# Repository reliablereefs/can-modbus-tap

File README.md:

# CAN / MODBUS tap

Listen-only probe for a 24 V accessory port that uses a USB-A shell. An ESP32-S3 records classic CAN frames, a collector stores them, and MODBUS RTU payloads inside those frames are decoded into request/response pairs and a register map.

The probe cannot transmit. The isolated CAN transceiver's TXD pin is tied to its logic supply, so the driver stays recessive, and the ESP32 TWAI controller runs in listen-only mode. Use it on equipment you are allowed to monitor.

## Bring-up before any connection

The USB-A plug is not USB. Do not plug it into a computer, and do not use a normal USB cable between the equipment port and anything else. A 24 V pin in that shell will damage a USB host.

1. With the tap unplugged, meter the equipment port.
2. Identify ground and the pin that sits near 24 V.
3. Scope the other two pins. Classic CAN idle holds both near 2.5 V. RS-485 idle is a differential offset without that 2.5 V pair bias.
4. Wire the tap's USB-A plug to match the measured port: pin 1 = 24 V, pin 2 = CANL, pin 3 = CANH, pin 4 = GND. See [docs/hardware.md](docs/hardware.md).
5. Power the tap from its USB-C port. The 24 V pin is measured and is not the tap's supply.
6. Confirm frames in the collector before trusting a bitrate lock.

If the scope does not show CAN bias, stop. This board's controller only decodes classic CAN. An RS-485 MODBUS RTU pair needs a different transceiver.

## Layout

```text
can-modbus-tap/
  docs/hardware.md     board, pinout, isolation, BOM notes
  docs/protocol.md     capture record, upload JSON, MODBUS pairing
  hardware/bom.csv
  firmware/            ESP-IDF project for ESP32-S3
  collector/           SQLite ingest, decode, and browser UI
```

```mermaid
flowchart LR
  port["Equipment port"] --> choke["Choke and TVS"]
  choke --> iso["ISO1042 TXD tied high"]
  iso --> esp["ESP32-S3 listen-only"]
  v24["24 V divider"] --> adc["ADS1115"]
  adc --> i2c["ISO1640"]
  i2c --> esp
  esp --> flash["Flash ring"]
  esp --> col["Collector"]
```

## Firmware

Requires ESP-IDF 5.3. The Wi-Fi SSID and collector URL are compile-time settings, so they stay out of the git tree.

```bash
cd firmware
idf.py set-target esp32s3
idf.py menuconfig   # CAN MODBUS Tap
idf.py build flash monitor
```

Set the SSID, password, and `TAP_COLLECTOR_URL`. Leave bitrate at 0 to scan 25 kbit/s through 1 Mbit/s. Set a fixed rate once the bus is identified. An empty SSID still records to the on-module flash ring.

The activity LED (GPIO2) stays on while frames arrive. GPIO5 is the TWAI transmit test point and is not routed to the transceiver.

## Collector

```bash
cd collector
go run ./cmd/collector -listen 0.0.0.0:8080 -db data/tap.db
```

Open `http://127.0.0.1:8080/`. Pages:

| Path | Contents |
| --- | --- |
| `/` | Raw CAN frames |
| `/modbus` | CRC-valid MODBUS RTU payloads |
| `/transactions` | Request paired with the next response, 500 ms window |
| `/map` | Register addresses sorted by how often they appear |
| `/v1/frames.csv` | Recent raw frames |

`POST /v1/frames` has no authentication. Run the collector on the lab network. Details are in [docs/protocol.md](docs/protocol.md).

```bash
cd collector && go test ./...
```

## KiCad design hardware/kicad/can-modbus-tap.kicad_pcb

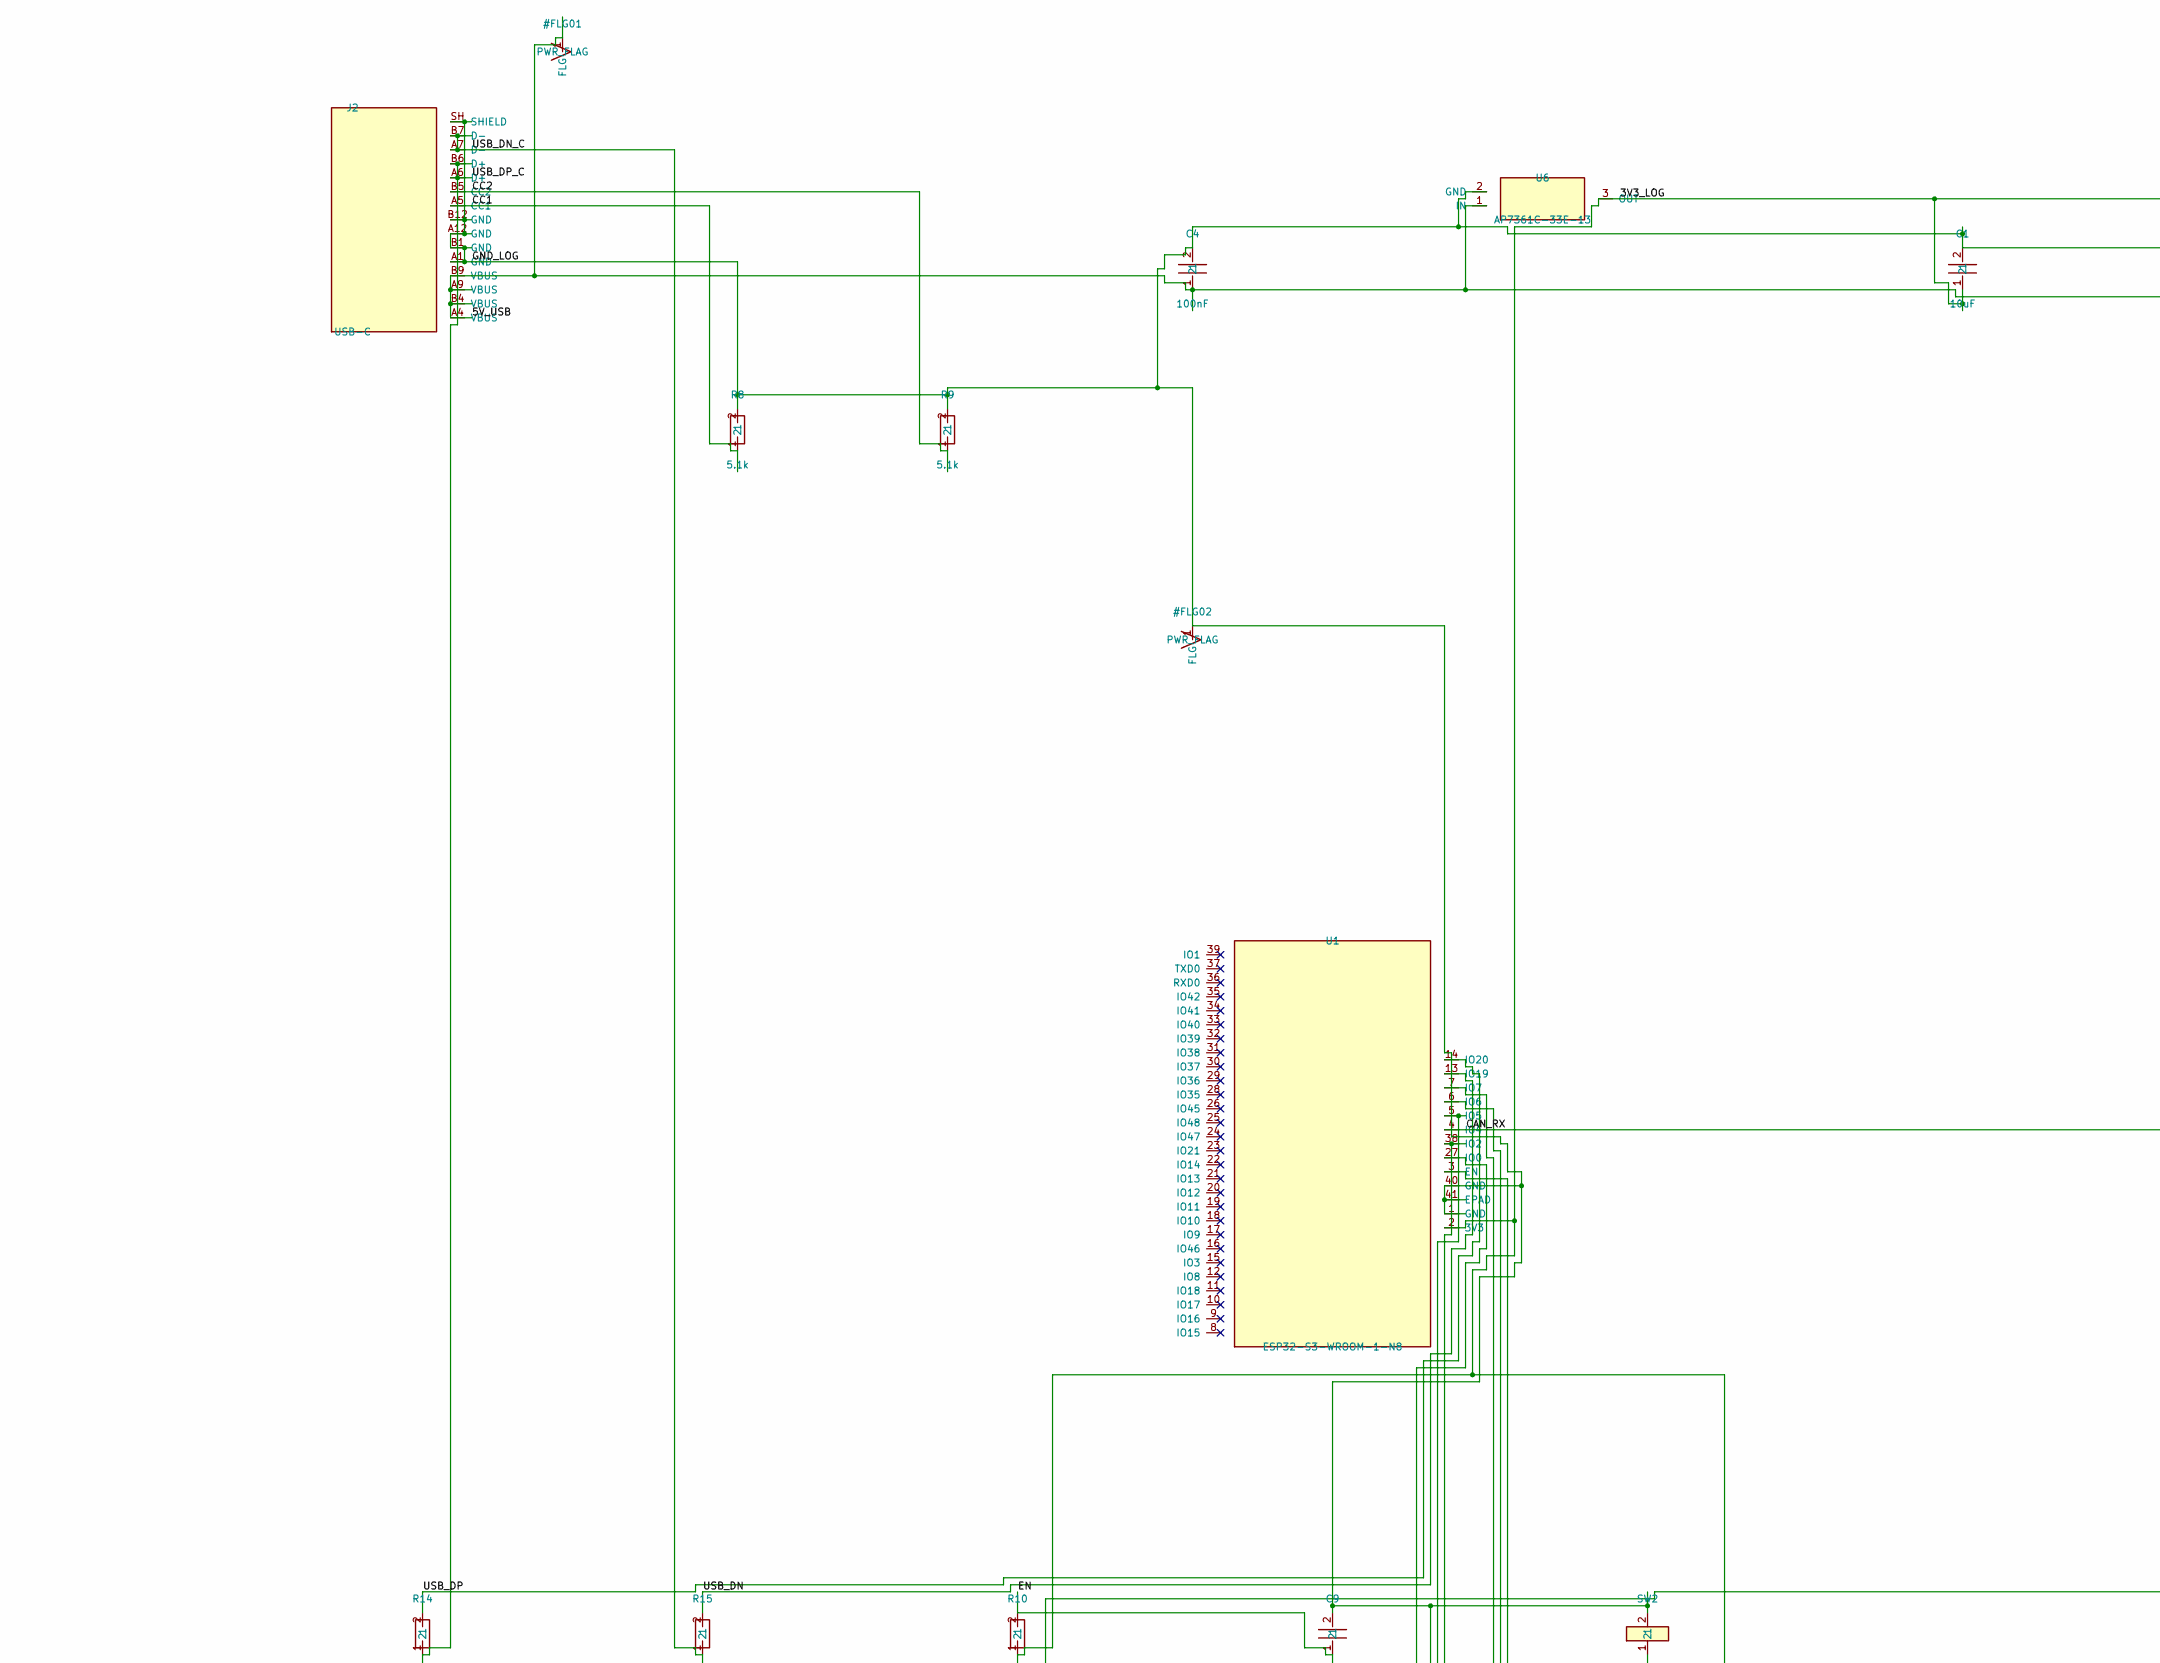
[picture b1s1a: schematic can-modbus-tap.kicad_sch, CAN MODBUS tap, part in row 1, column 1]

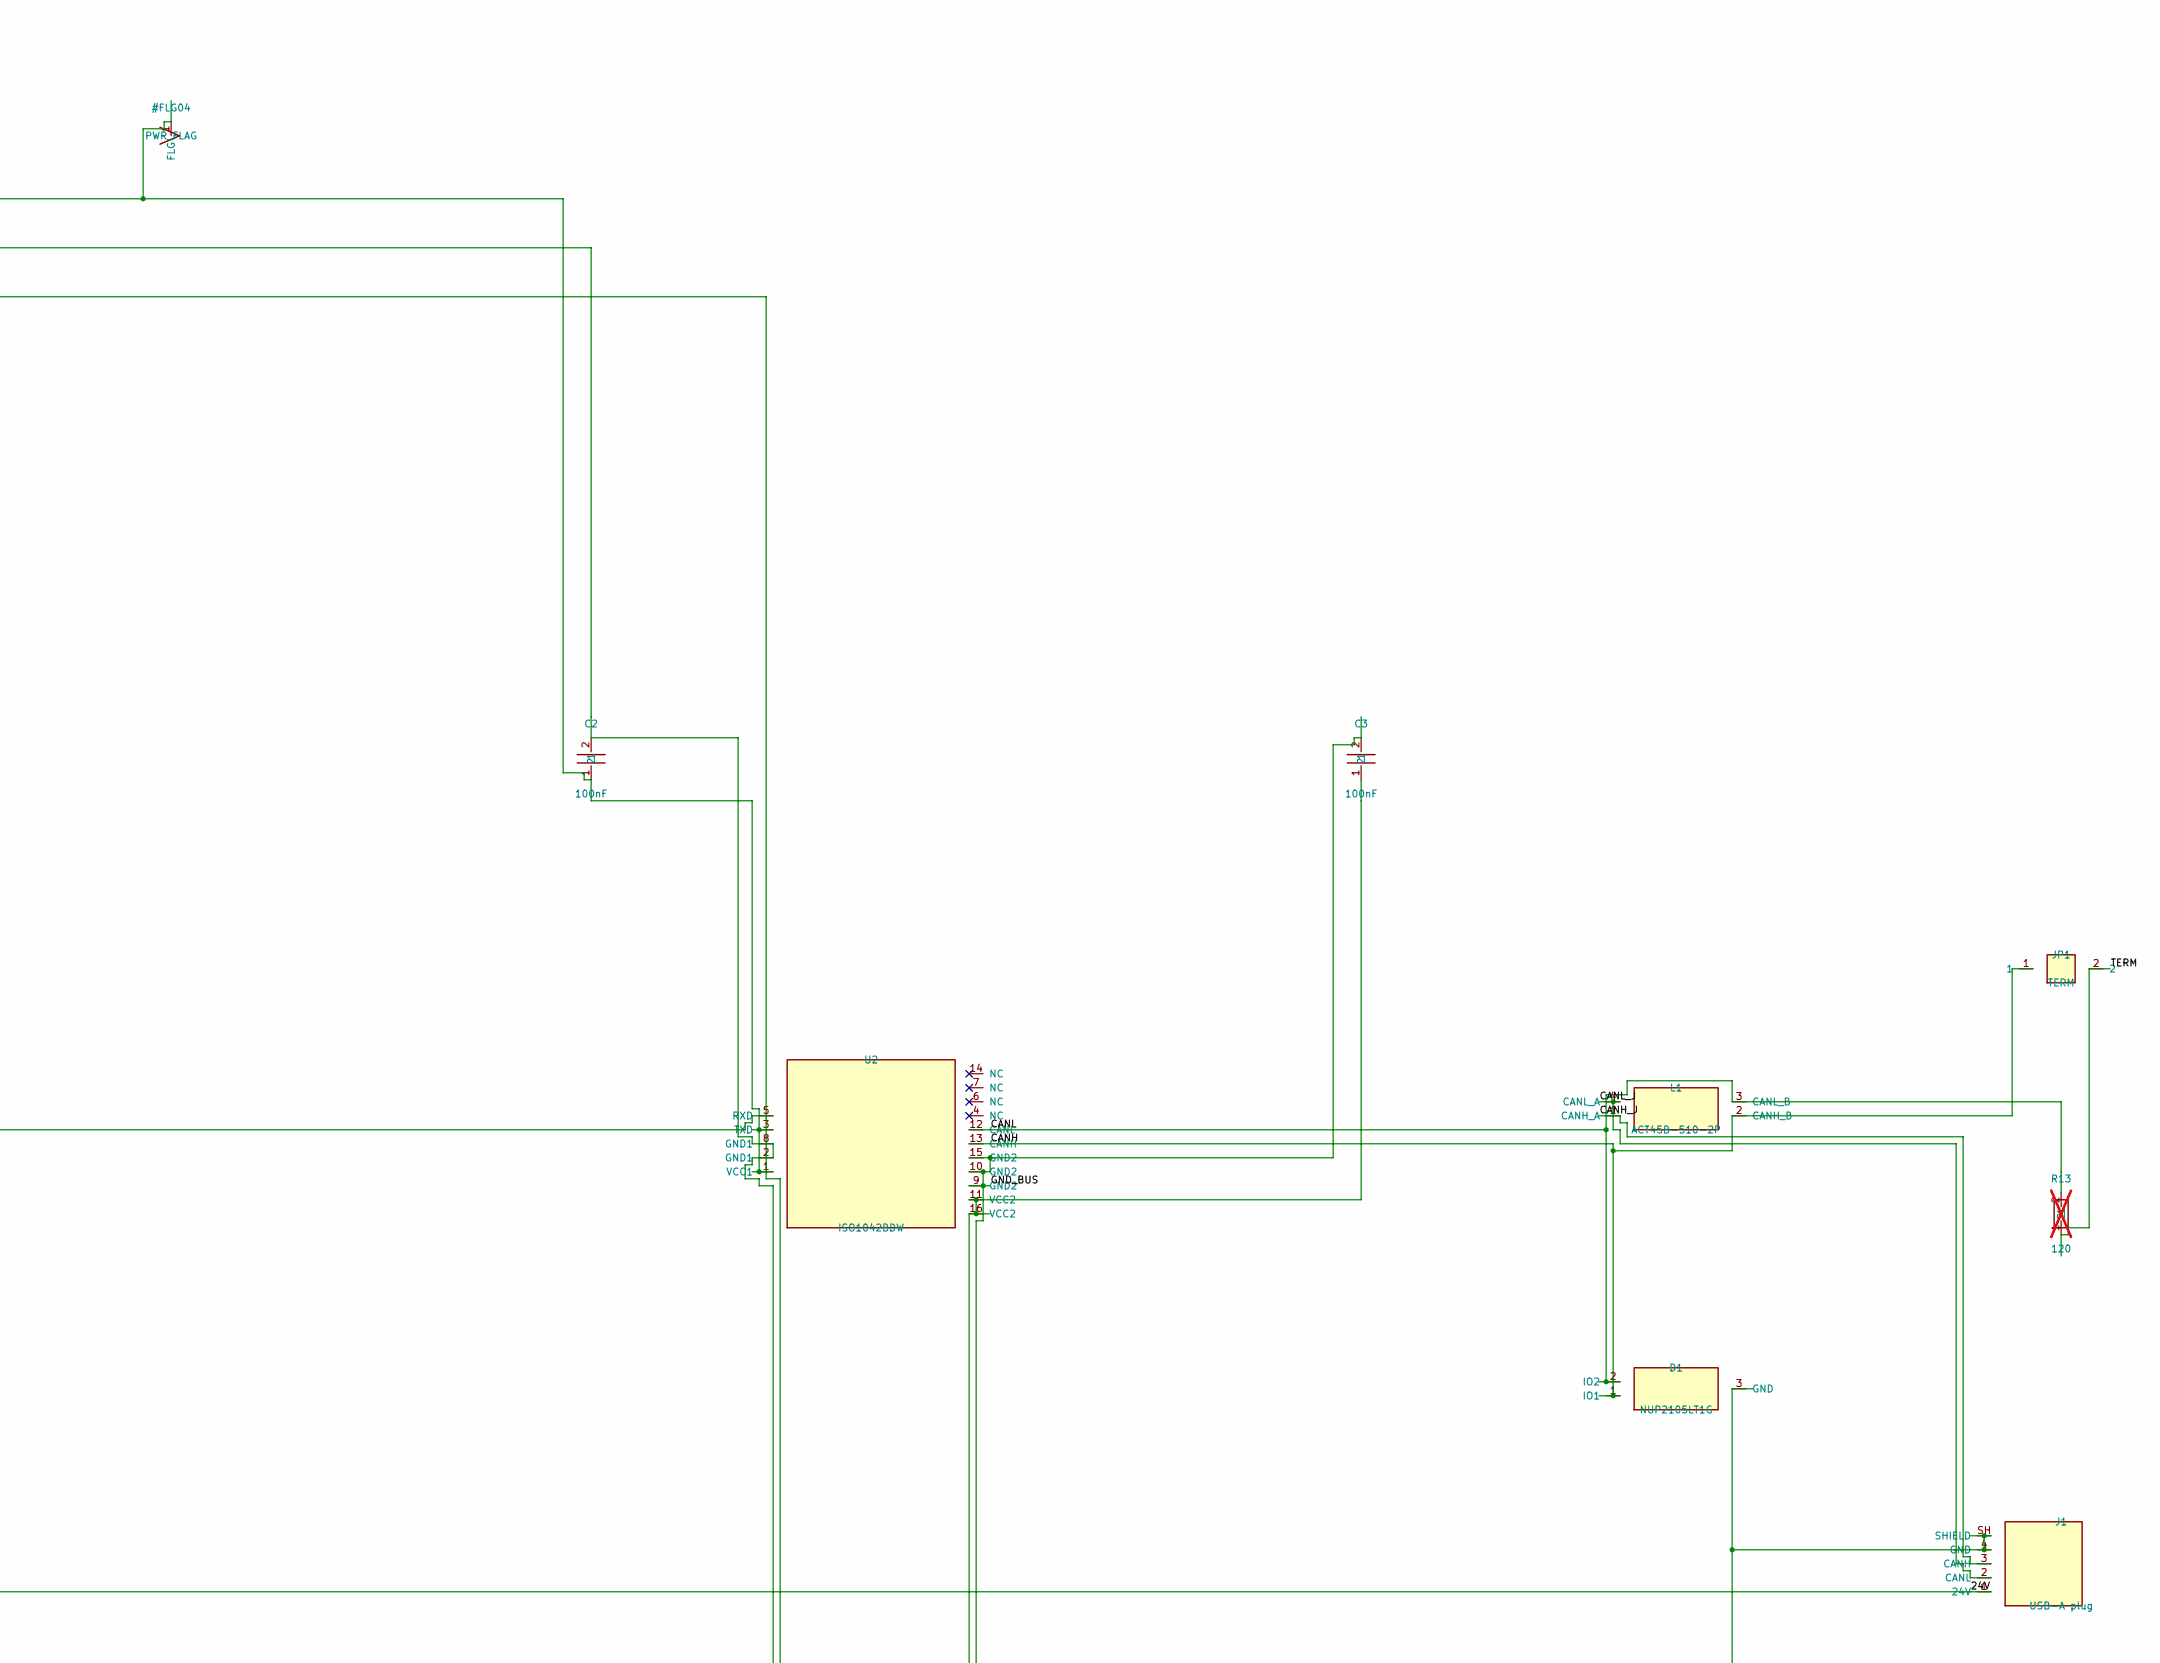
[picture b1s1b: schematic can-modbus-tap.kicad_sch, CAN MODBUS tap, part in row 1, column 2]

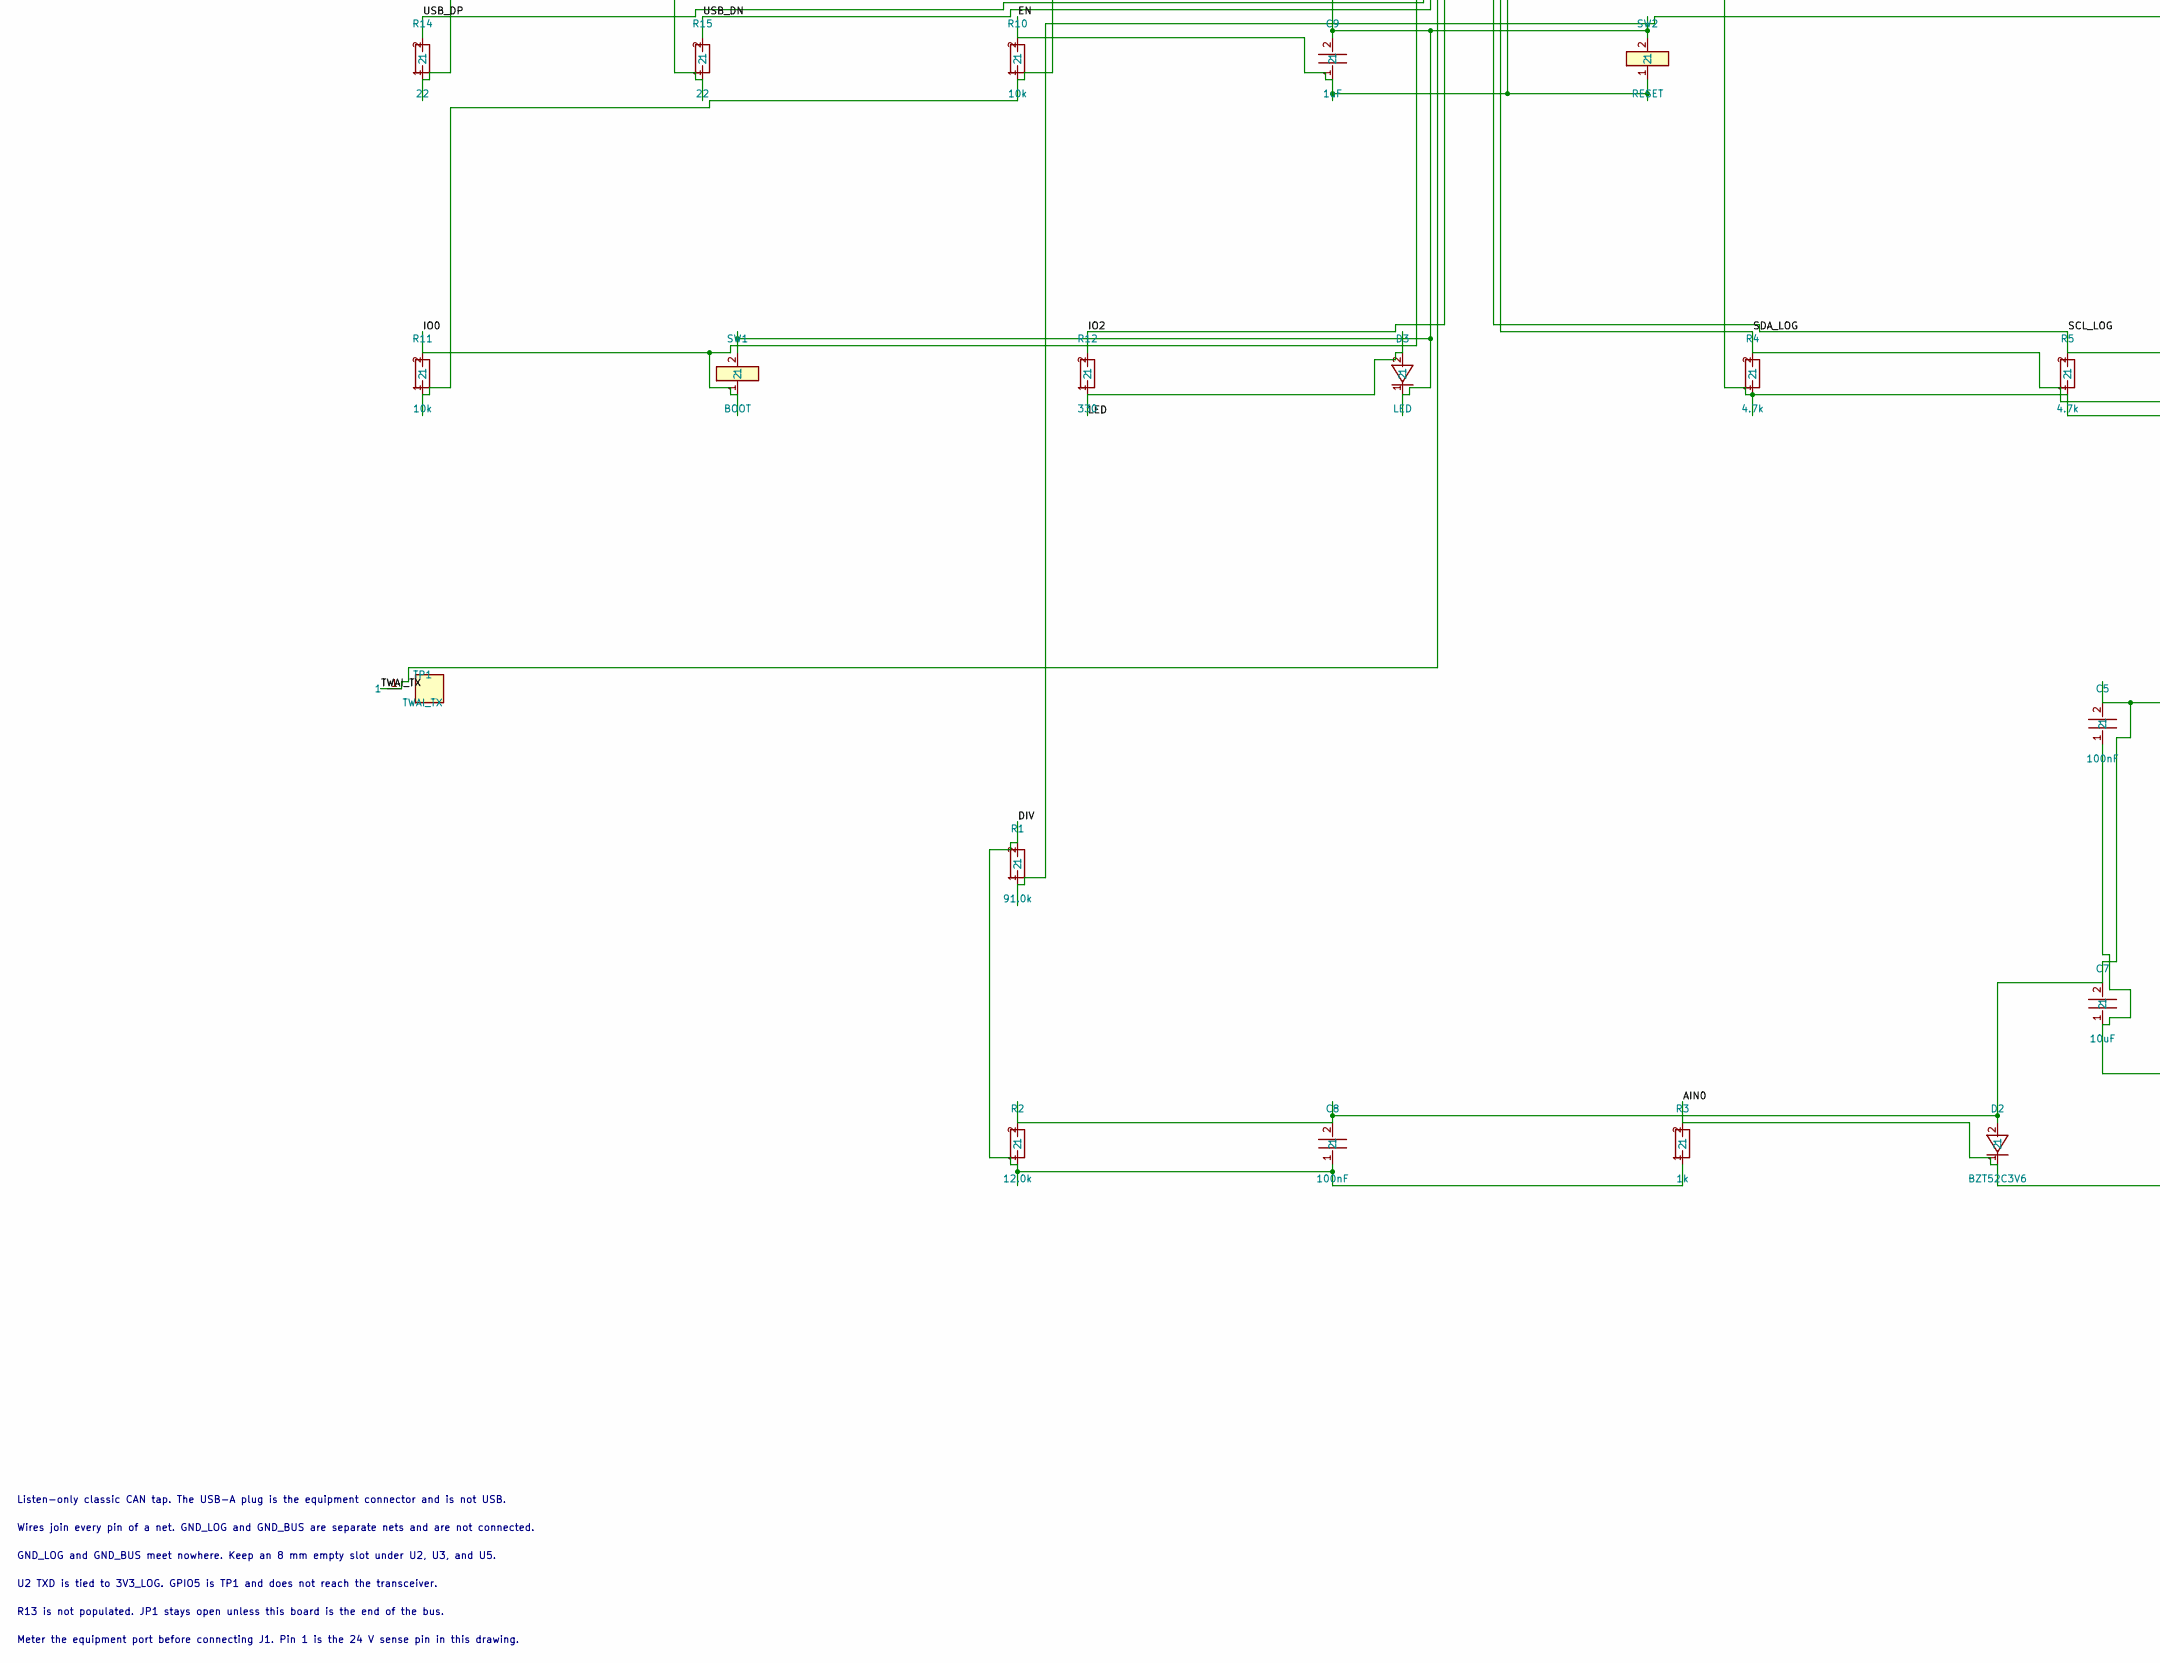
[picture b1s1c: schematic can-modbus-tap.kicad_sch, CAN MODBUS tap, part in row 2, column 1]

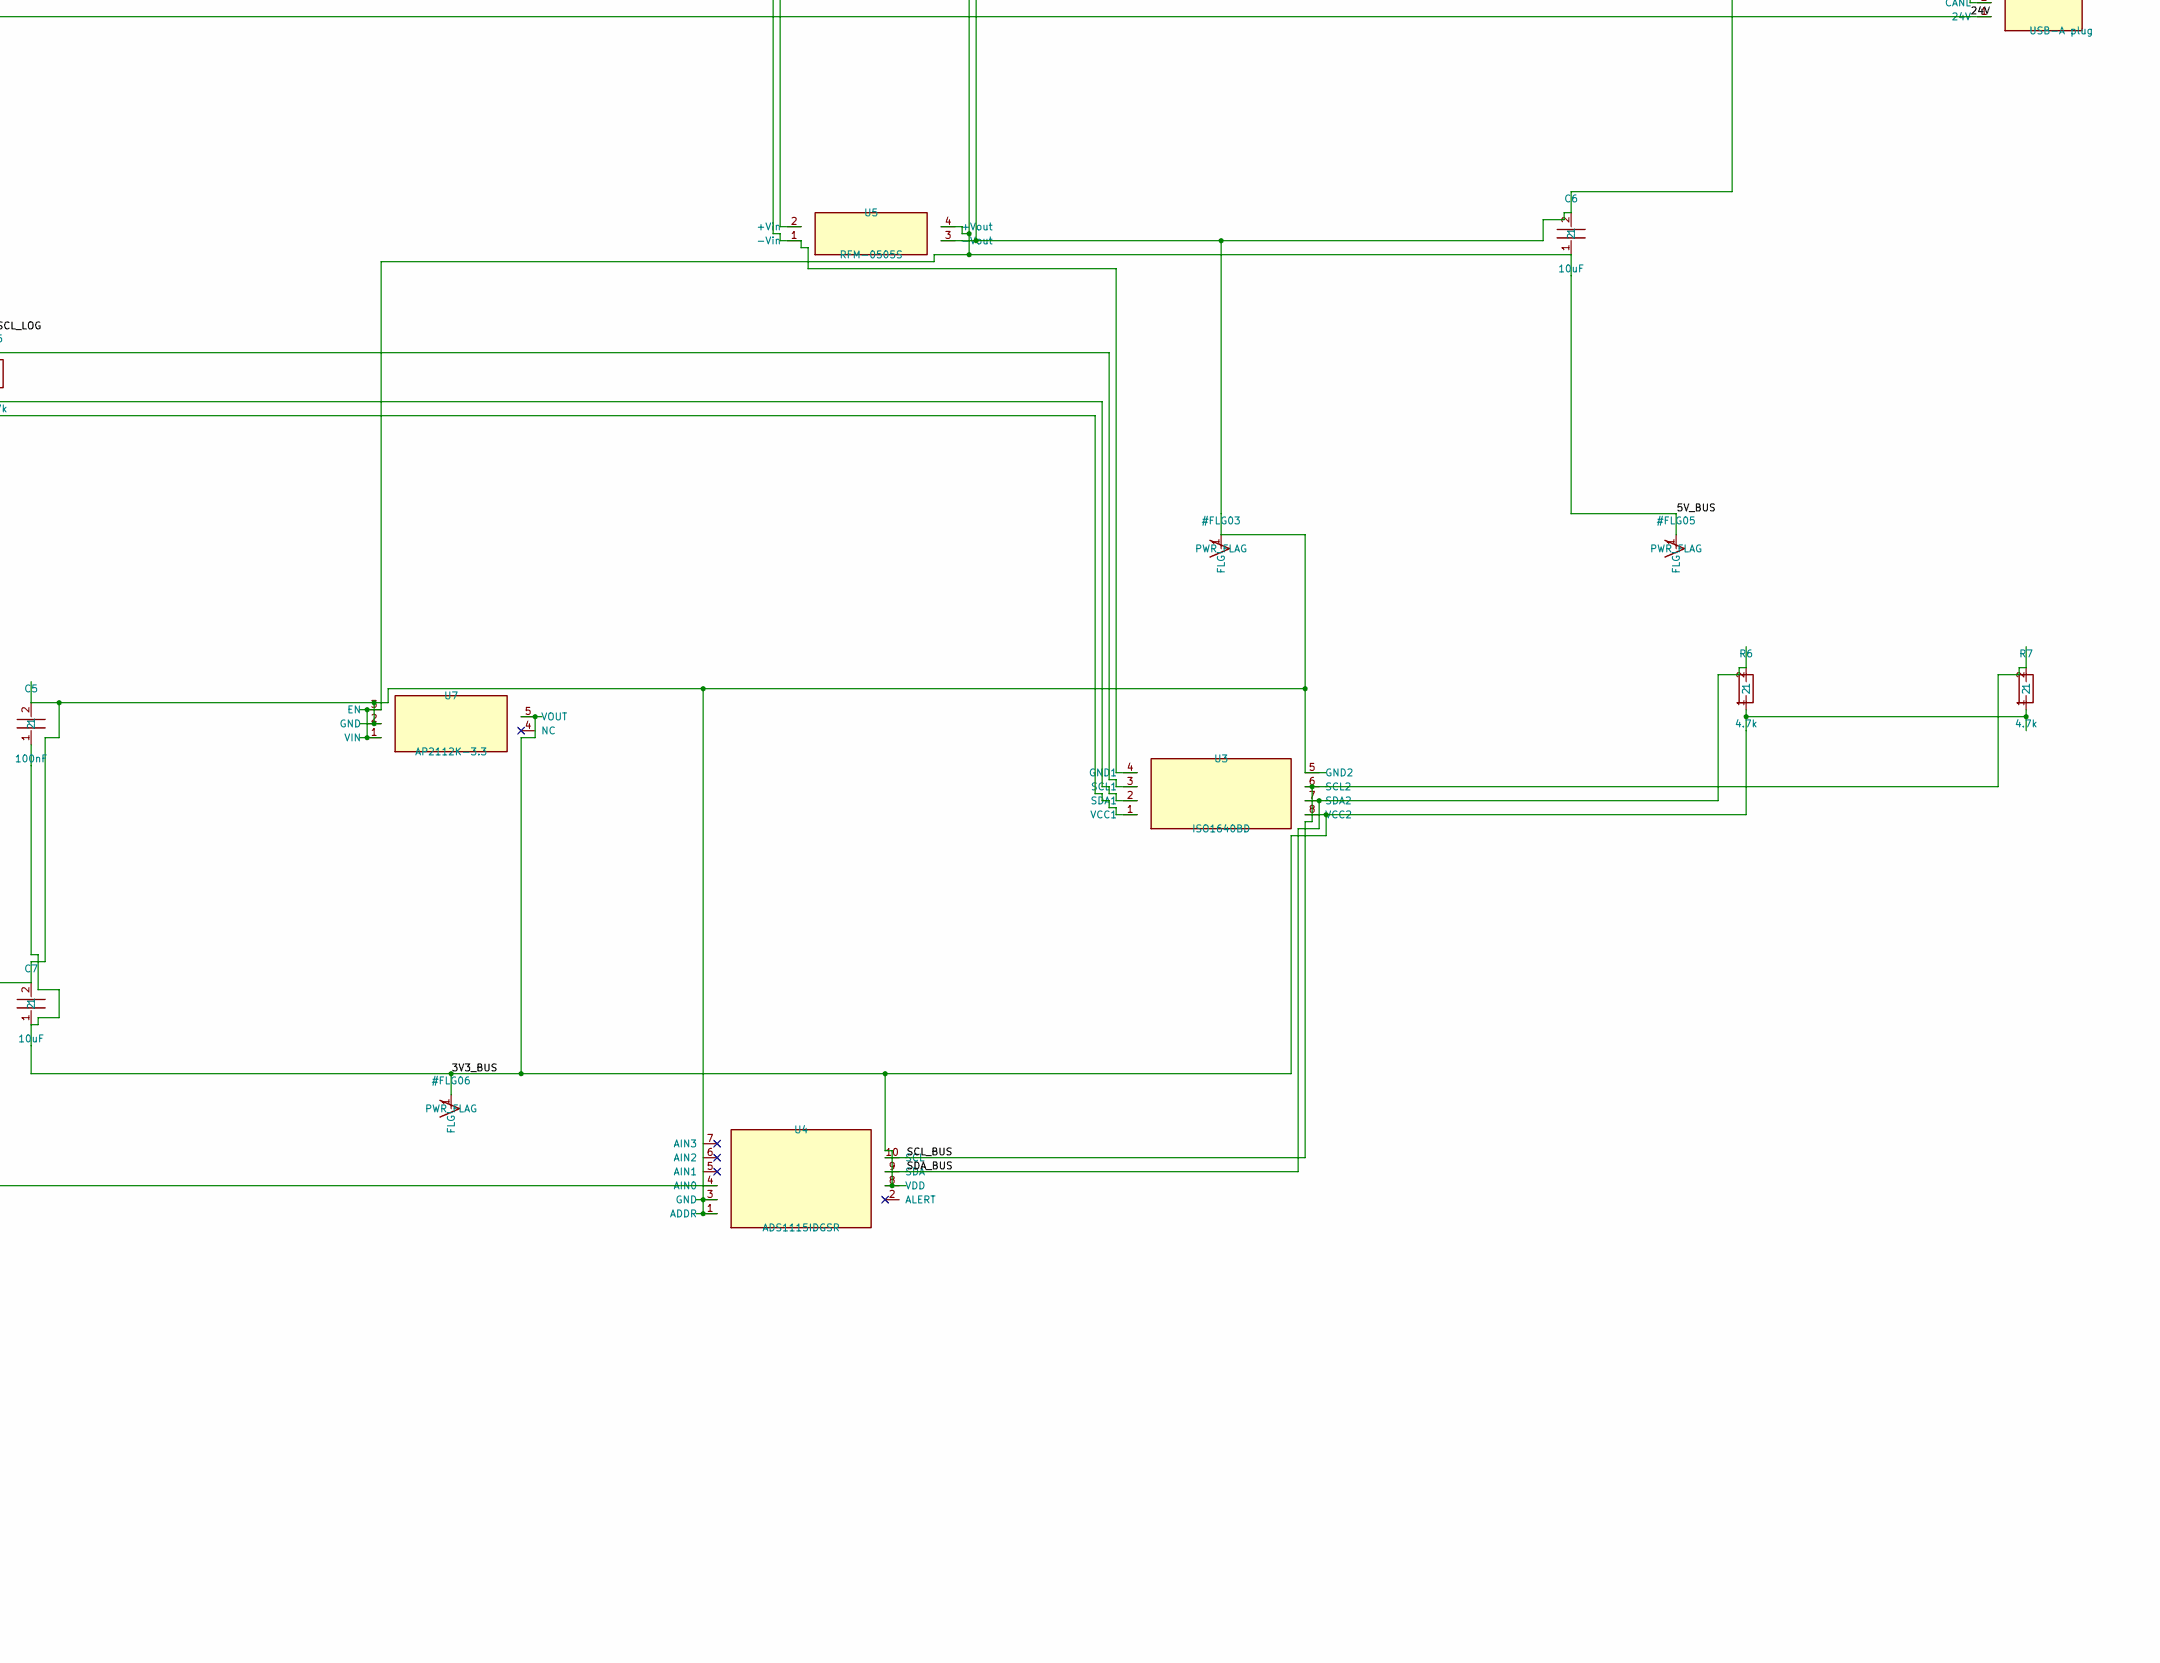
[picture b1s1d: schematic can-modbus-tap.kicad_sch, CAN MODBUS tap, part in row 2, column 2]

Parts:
C1, C6, C7: 10uF; C_0805_2012Metric
C2, C3, C4, C5, C8: 100nF; C_0402_1005Metric
C9: 1uF; C_0402_1005Metric
D1: NUP2105LT1G; SOT-23
D2: BZT52C3V6; D_SOD-123
D3: LED; LED_0603_1608Metric
J1: USB-A plug; USB3_A_Plug_Wuerth_692112030100_Horizontal
J2: USB-C; USB_C_Receptacle_GCT_USB4105-xx-A_16P_TopMnt_Horizontal
JP1: TERM; PinHeader_1x02_P2.54mm_Vertical
L1: ACT45B-510-2P
R1: 91.0k; R_0603_1608Metric
R2: 12.0k; R_0603_1608Metric
R3: 1k; R_0603_1608Metric
R4, R5, R6, R7: 4.7k; R_0603_1608Metric
R8, R9: 5.1k; R_0603_1608Metric
R10, R11: 10k; R_0603_1608Metric
R12: 330; R_0603_1608Metric
R13: 120; R_0603_1608Metric; not fitted
R14, R15: 22; R_0603_1608Metric
SW1: BOOT; SW_PUSH_6mm
SW2: RESET; SW_PUSH_6mm
TP1: TWAI_TX; TestPoint_Pad_D1.5mm
U1: ESP32-S3-WROOM-1-N8; ESP32-S3-WROOM-1
U2: ISO1042BDW; SOIC-16W_7.5x10.3mm_P1.27mm
U3: ISO1640BD; SOIC-8_3.9x4.9mm_P1.27mm
U4: ADS1115IDGSR; MSOP-10_3x3mm_P0.5mm
U5: RFM-0505S; RECOM_RFM-0505S
U6: AP7361C-33E-13; SOT-223-3_TabPin2
U7: AP2112K-3.3; SOT-23-5

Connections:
3V3_BUS: C5.1, C7.1, R6.1, R7.1, U3.8 (VCC2), U4.8 (VDD), U7.5 (VOUT)
3V3_LOG: C1.1, C2.1, R4.1, R5.1, R10.1, R11.1, U1.2 (3V3), U2.1 (VCC1), U2.3 (TXD), U3.1 (VCC1), U6.3 (OUT)
5V_BUS: C3.1, C6.1, U2.11 (VCC2), U2.16 (VCC2), U5.4 (+Vout), U7.1 (VIN), U7.3 (EN)
5V_USB: C4.1, J2.A4 (VBUS), J2.A9 (VBUS), J2.B4 (VBUS), J2.B9 (VBUS), U5.2 (+Vin), U6.1 (IN)
24V: J1.1 (24V), R1.1
AIN0: D2.1, R3.2, U4.4 (AIN0)
CANH: D1.1 (IO1), JP1.1, L1.2 (CANH_B), U2.13 (CANH)
CANH_J: J1.3 (CANH), L1.1 (CANH_A)
CANL: D1.2 (IO2), L1.3 (CANL_B), R13.2, U2.12 (CANL)
CANL_J: J1.2 (CANL), L1.4 (CANL_A)
CAN_RX: U1.4 (IO4), U2.5 (RXD)
CC1: J2.A5 (CC1), R8.1
CC2: J2.B5 (CC2), R9.1
DIV: C8.1, R1.2, R2.1, R3.1
EN: C9.1, R10.2, SW2.1, U1.3 (EN)
GND_BUS: C3.2, C5.2, C6.2, C7.2, C8.2, D1.3 (GND), D2.2, J1.4 (GND), J1.SH (SHIELD), R2.2, U2.9 (GND2), U2.10 (GND2), U2.15 (GND2), U3.5 (GND2), U4.1 (ADDR), U4.3 (GND), U5.3 (-Vout), U7.2 (GND)
GND_LOG: C1.2, C2.2, C4.2, C9.2, D3.1, J2.A1 (GND), J2.A12 (GND), J2.B1 (GND), J2.B12 (GND), J2.SH (SHIELD), R8.2, R9.2, SW1.2, SW2.2, U1.1 (GND), U1.40 (GND), U1.41 (EPAD), U2.2 (GND1), U2.8 (GND1), U3.4 (GND1), U5.1 (-Vin), U6.2 (GND)
IO0: R11.2, SW1.1, U1.27 (IO0)
IO2: R12.2, U1.38 (IO2)
LED: D3.2, R12.1
SCL_BUS: R7.2, U3.6 (SCL2), U4.10 (SCL)
SCL_LOG: R5.2, U1.7 (IO7), U3.3 (SCL1)
SDA_BUS: R6.2, U3.7 (SDA2), U4.9 (SDA)
SDA_LOG: R4.2, U1.6 (IO6), U3.2 (SDA1)
TERM: JP1.2, R13.1
TWAI_TX: TP1.1, U1.5 (IO5)
USB_DN: R15.2, U1.13 (IO19)
USB_DN_C: J2.A7 (D-), J2.B7 (D-), R15.1
USB_DP: R14.2, U1.14 (IO20)
USB_DP_C: J2.A6 (D+), J2.B6 (D+), R14.1

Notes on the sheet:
Listen-only classic CAN tap. The USB-A plug is the equipment connector and is not USB.
Wires join every pin of a net. GND_LOG and GND_BUS are separate nets and are not connected.
GND_LOG and GND_BUS meet nowhere. Keep an 8 mm empty slot under U2, U3, and U5.
U2 TXD is tied to 3V3_LOG. GPIO5 is TP1 and does not reach the transceiver.
R13 is not populated. JP1 stays open unless this board is the end of the bus.
Meter the equipment port before connecting J1. Pin 1 is the 24 V sense pin in this drawing.

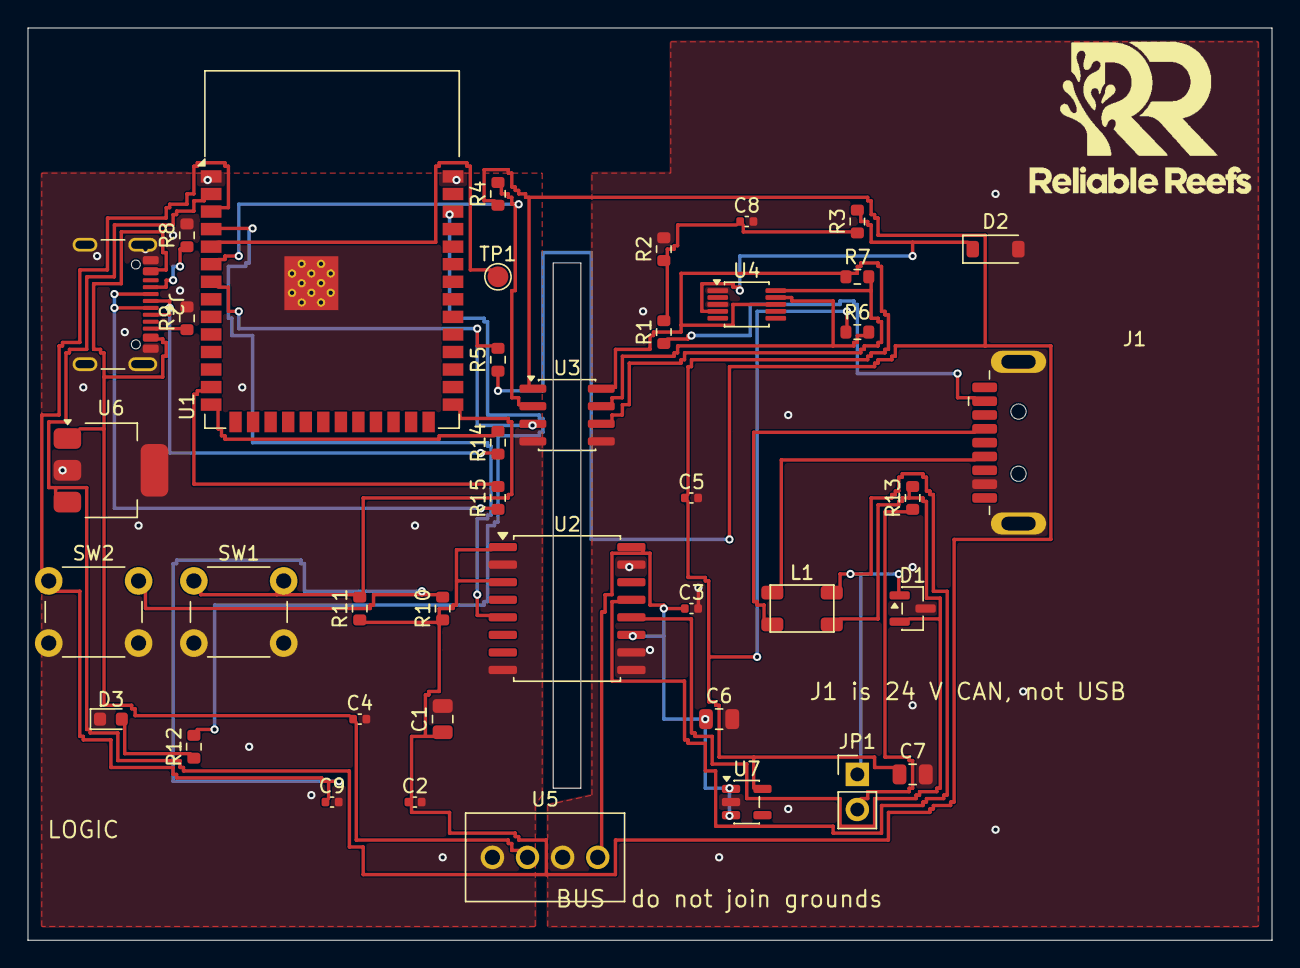
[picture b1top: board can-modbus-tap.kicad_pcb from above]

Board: 2 copper layers, 90.0 x 66.0 mm, 41 parts (0 on the bottom side), 30 nets.

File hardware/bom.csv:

Qty,Ref,Value,Package,Manufacturer,Part,Notes
1,U1,ESP32-S3-WROOM-1-N8,Module,Espressif,ESP32-S3-WROOM-1-N8,8 MB quad flash. Classic CAN only.
1,U2,ISO1042,SOIC-16,Texas Instruments,ISO1042BDW,"Isolated CAN. TXD hard-tied to VCC1. Tie VCC2 pins 11 and 16."
1,U3,I2C isolator,SOIC-8,Texas Instruments,ISO1640BD,Bus-side ADS1115 to ESP32. 3.3 V both sides.
1,U4,ADC 16-bit,VSSOP-10,Texas Instruments,ADS1115IDGSR,ADDR to bus GND. AIN0 is the 24 V divider.
1,U5,5V to 5V 1W isolated,SIP4,RECOM,RFM-0505S,"Pin 1 -Vin, 2 +Vin, 3 -Vout, 4 +Vout. RECOM rates it 1 kVDC."
1,U6,3.3V 1A LDO,SOT-223,Diodes Inc,AP7361C-33E-13,USB VBUS to ESP32 3.3 V.
1,U7,3.3V 600mA LDO,SOT-23-5,Diodes Inc,AP2112K-3.3TRG1,Bus-side 5 V to 3.3 V for ADS1115 and ISO1640 side 2.
1,J1,USB-A plug,USB3-A horizontal,Würth,692112030100,Field connector. Not a USB port. See docs/hardware.md pinout.
1,J2,USB-C receptacle,USB-C 16P top-mount,GCT,USB4105,Logic power and native USB programming.
1,L1,CAN common-mode choke,ACT45B,TDK,ACT45B-510-2P-TL003,Between J1 and U2.
1,D1,CAN TVS,SOT-23,onsemi,NUP2105LT1G,CANH CANL and bus GND.
1,D2,3.6V zener,SOD-123,Nexperia,BZT52C3V6,Clamp ADS1115 AIN0 to bus GND.
1,D3,LED,0603,,,Activity. On while frames are arriving.
2,SW1 SW2,Tactile,6mm,,,SW1 BOOT to GPIO0. SW2 reset to EN.
1,R1,91.0k 1%,0603,,,24 V divider top. Bus side only.
1,R2,12.0k 1%,0603,,,24 V divider bottom.
1,R3,1k,0603,,,Series into ADS1115 AIN0.
2,R4 R5,4.7k,0603,,,I2C pull-ups on the logic side to 3V3_LOG.
2,R6 R7,4.7k,0603,,,I2C pull-ups on the bus side to 3V3_BUS.
2,R8 R9,5.1k,0603,,,USB-C CC1 and CC2 to logic GND.
2,R10 R11,10k,0603,,,EN and GPIO0 pull-ups to 3V3_LOG.
1,R12,330,0603,,,LED series.
1,R13,120 1%,0603,,,DNP. Termination footprint. Leave open.
2,R14 R15,22,0603,,,USB D+ and D- series. Optional but recommended.
1,C1,10uF 10V,0805,,,3V3_LOG bulk.
4,C2 C3 C4 C5,100nF,0402,,,U2 VCC1 U2 VCC2 U6 U7.
2,C6 C7,10uF 10V,0805,,,5V_BUS and 3V3_BUS bulk.
1,C8,100nF,0402,,,Across R2.
1,C9,1uF,0402,,,EN to logic GND.
1,JP1,Termination jumper,0.1in header,,,Open. Stuff only if this node is a physical bus end.
1,TP1,TWAI TX test point,Pad,,,GPIO5. Not connected to the transceiver.

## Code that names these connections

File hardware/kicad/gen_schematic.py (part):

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        Inst("tap:NUP2105", "D1", "NUP2105LT1G", "Package_TO_SOT_SMD:SOT-23", {
            "1": "CANH", "2": "CANL", "3": gnd_b,
        }),
        Inst("tap:JP", "JP1", "TERM", "Connector_PinHeader_2.54mm:PinHeader_1x02_P2.54mm_Vertical", {
            "1": "CANH", "2": "TERM",
        }, description="Leave open. Close only at the physical end of the bus."),
        Inst("tap:R", "R13", "120", "Resistor_SMD:R_0603_1608Metric", {"1": "TERM", "2": "CANL"}, dnp=True,
             description="DNP. In series with JP1."),
        Inst("tap:USB-A", "J1", "USB-A plug", "Connector_USB:USB3_A_Plug_Wuerth_692112030100_Horizontal", {
            "1": "24V", "2": "CANL_J", "3": "CANH_J", "4": gnd_b, "SH": gnd_b,
        }, description="Male plug, not a receptacle. Pin 1 is +24 V sense, pin 2 CANL, pin 3 CANH, pin 4 GND, shell is bus ground."),
        Inst("tap:RFM", "U5", "RFM-0505S", "can-modbus-tap:RECOM_RFM-0505S", {
            "1": gnd_l, "2": v5, "3": gnd_b, "4": v5b,
        }, description="SIP4. Pin 1 -Vin, 2 +Vin, 3 -Vout, 4 +Vout. RECOM rates this module 1 kVDC."),
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        Inst("tap:R", "R2", "12.0k", "Resistor_SMD:R_0603_1608Metric", {"1": "DIV", "2": gnd_b}),
        Inst("tap:C", "C8", "100nF", "Capacitor_SMD:C_0402_1005Metric", {"1": "DIV", "2": gnd_b}),
        Inst("tap:R", "R3", "1k", "Resistor_SMD:R_0603_1608Metric", {"1": "DIV", "2": "AIN0"}),
        Inst("tap:D", "D2", "BZT52C3V6", "Diode_SMD:D_SOD-123", {"1": "AIN0", "2": gnd_b}, description="Pin 1 is the cathode, at AIN0. Pin 2 is the anode, at bus ground."),
        Inst("tap:ADS1115", "U4", "ADS1115IDGSR", "Package_SO:MSOP-10_3x3mm_P0.5mm", {
            "1": gnd_b, "3": gnd_b, "4": "AIN0", "5": None, "6": None, "7": None,
            "2": None, "8": v3b, "9": "SDA_BUS", "10": "SCL_BUS",
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    for pin, net in checks.items():
        if pin_net.get(pin) != net:
            raise SystemExit(f"{pin} is {pin_net.get(pin)}, expected {net}")
    if "TWAI_TX" in {pin_net.get("U2.3"), pin_net.get("U2.5")}:
        raise SystemExit("transceiver is connected to TWAI_TX")
    if not any(part.ref == "R13" and part.dnp for part in parts):
        raise SystemExit("R13 must be DNP")
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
